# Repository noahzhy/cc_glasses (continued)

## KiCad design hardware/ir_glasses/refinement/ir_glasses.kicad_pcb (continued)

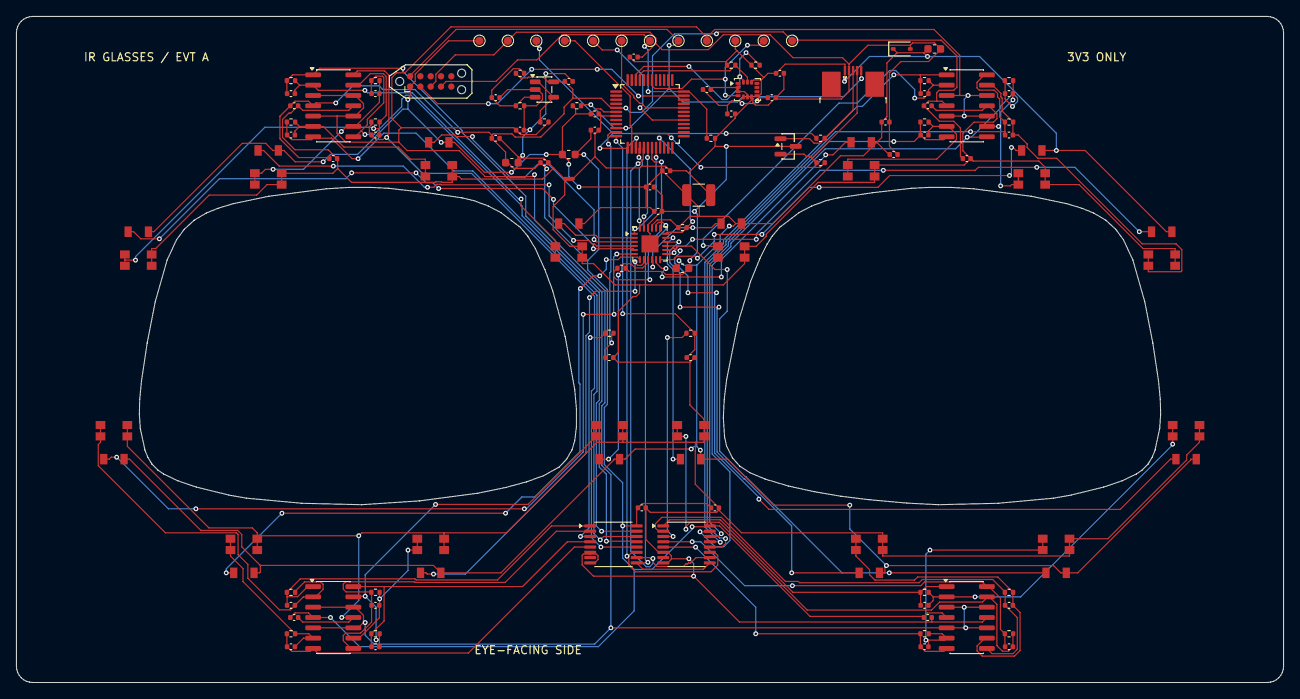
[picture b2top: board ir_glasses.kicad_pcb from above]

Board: 2 copper layers, 156.0 x 82.0 mm, 136 parts (0 on the bottom side), 79 nets.

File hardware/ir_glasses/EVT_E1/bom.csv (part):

Reference,Value,Footprint,Quantity,Populate,X_mm,Y_mm,Rotation_deg,Side,Manufacturer,MPN,LCSC
U9,STM32C031C6T6,IR_Glasses:LQFP-48_7x7mm_P0.5mm,1,Yes,110,63,0,front,STMicroelectronics,STM32C031C6T6,C5456218
U1,TLC59283RGER,IR_Glasses:Texas_RGE0024C_VQFN-24-1EP_4x4mm_P0.5mm_EP2.1x2.1mm,1,Yes,121,62,0,front,Texas Instruments,TLC59283RGER,C485815
U10,LSM6DS3TR-C,IR_Glasses:LGA-14_3x2.5mm_P0.5mm_LayoutBorder3x4y,1,Yes,110,71.3,0,front,STMicroelectronics,LSM6DS3TR-C,C967633
U6,TLV9061IDBVR,IR_Glasses:SOT-23-5,1,Yes,87,62,0,front,Texas Instruments,TLV9061IDBVR,C398358
J1,2492111-5,IR_Glasses:TE_2492111-5_1x05_P0.5mm_Horizontal,1,Yes,165,61.7,180,front,TE Connectivity,2492111-5,
J2,TC2050-IDC-NL / ARM2010,IR_Glasses:Tag-Connect_TC2050-IDC-NL_2x05_P1.27mm_Vertical,1,PCB pads only,55.5,61,0,front,,,
U11,"PESD3V3L2BT,215",IR_Glasses:SOT-23,1,Yes,167.5,67.0,0,front,Nexperia,"PESD3V3L2BT,215",C55440
D17,"PESD5V0S1BA,115",IR_Glasses:D_SOD-323,1,Yes,159.0,60.0,90,front,Nexperia,"PESD5V0S1BA,115",C19224
FB1,600R@100MHz 500mA,IR_Glasses:L_0603_1608Metric,1,Yes,89.0,67.0,0,front,Murata,BLM18AG601SN1D,C19330
NT1,AGND-GND star,IR_Glasses:NetTie-2_SMD_Pad0.5mm,1,PCB pads only,92.0,67.0,0,front,,,
R1,2.67k,IR_Glasses:R_0402_1005Metric,1,Yes,125.75,63.25,90,front,Viking,ARG02FTC2671,C284464
R2,10k,IR_Glasses:R_0402_1005Metric,1,Yes,85.0,59.5,0,front,UNI-ROYAL,0402WGF1002TCE,C25744
R3,10k,IR_Glasses:R_0402_1005Metric,1,Yes,86.0,64.5,0,front,UNI-ROYAL,0402WGF1002TCE,C25744
R4,10k,IR_Glasses:R_0402_1005Metric,1,Yes,103.5,61.0,0,front,UNI-ROYAL,0402WGF1002TCE,C25744
R5,100k,IR_Glasses:R_0402_1005Metric,1,Yes,115.8,61.0,90,front,UNI-ROYAL,0402WGF1003TCE,C25741
R6,4.7k,IR_Glasses:R_0402_1005Metric,1,Yes,113.0,70.0,0,front,UNI-ROYAL,0402WGF4701TCE,C25900
R7,4.7k,IR_Glasses:R_0402_1005Metric,1,Yes,113.5,72.0,90,front,UNI-ROYAL,0402WGF4701TCE,C25900
R8,22,IR_Glasses:R_0402_1005Metric,1,Yes,154.0,66.0,0,front,UNI-ROYAL,0402WGF220JTCE,C25092
R9,22,IR_Glasses:R_0402_1005Metric,1,Yes,170.0,69.5,0,front,UNI-ROYAL,0402WGF220JTCE,C25092
R10,10k,IR_Glasses:R_0402_1005Metric,1,Yes,125.75,60.0,90,front,UNI-ROYAL,0402WGF1002TCE,C25744
R11,100,IR_Glasses:R_0402_1005Metric,1,Yes,102.0,67.0,0,front,UNI-ROYAL,0402WGF1000TCE,C25076
R12,100,IR_Glasses:R_0402_1005Metric,1,Yes,116.0,67.0,90,front,UNI-ROYAL,0402WGF1000TCE,C25076
R13,47,IR_Glasses:R_0402_1005Metric,1,Yes,89.75,60.0,90,front,UNI-ROYAL,0402WGF470JTCE,C25118
U2,TLV9064IPWR,IR_Glasses:TSSOP-14_4.4x5mm_P0.65mm,1,Yes,77.5,60.5,0,front,Texas Instruments,TLV9064IPWR,C779410
U3,TLV9064IPWR,IR_Glasses:TSSOP-14_4.4x5mm_P0.65mm,1,Yes,67,61.4,0,front,Texas Instruments,TLV9064IPWR,C779410
PD1,PD15-22B/TR8,IR_Glasses:Everlight_PD15_22B,1,Yes,99.1474,94.9322,69.734,front,Everlight,PD15-22B/TR8,C161211
D1,IR11-21C/TR8,IR_Glasses:Everlight_IR11_21C,1,Yes,97.2266,99.389,61.38,front,Everlight,IR11-21C/TR8,C16745
RF1,100k,IR_Glasses:R_0402_1005Metric,1,Yes,72.888,58.875,90,front,UNI-ROYAL,0402WGF1003TCE,C25741
CF1,22p C0G,IR_Glasses:C_0402_1005Metric,1,Yes,72.888,60.875,90,front,FH,0402CG220J500NT,C1555
PD2,PD15-22B/TR8,IR_Glasses:Everlight_PD15_22B,1,Yes,86.2915,106.4166,9.481,front,Everlight,PD15-22B/TR8,C161211
D2,IR11-21C/TR8,IR_Glasses:Everlight_IR11_21C,1,Yes,81.3647,107.0997,6.53,front,Everlight,IR11-21C/TR8,C16745
RF2,100k,IR_Glasses:R_0402_1005Metric,1,Yes,74.638,63.875,0,front,UNI-ROYAL,0402WGF1003TCE,C25741
CF2,22p C0G,IR_Glasses:C_0402_1005Metric,1,Yes,72.888,62.875,90,front,FH,0402CG220J500NT,C1555
PD3,PD15-22B/TR8,IR_Glasses:Everlight_PD15_22B,1,Yes,65.5404,106.8475,-7.387,front,Everlight,PD15-22B/TR8,C161211
D3,IR11-21C/TR8,IR_Glasses:Everlight_IR11_21C,1,Yes,60.667,106.0473,-11.779,front,Everlight,IR11-21C/TR8,C16745
RF3,100k,IR_Glasses:R_0402_1005Metric,1,Yes,82.112,62.125,90,front,UNI-ROYAL,0402WGF1003TCE,C25741
CF3,22p C0G,IR_Glasses:C_0402_1005Metric,1,Yes,82.112,60.125,90,front,FH,0402CG220J500NT,C1555
PD4,PD15-22B/TR8,IR_Glasses:Everlight_PD15_22B,1,Yes,49.5328,98.7372,-65.946,front,Everlight,PD15-22B/TR8,C161211
D4,IR11-21C/TR8,IR_Glasses:Everlight_IR11_21C,1,Yes,48.0093,94.1124,-74.093,front,Everlight,IR11-21C/TR8,C16745
RF4,100k,IR_Glasses:R_0402_1005Metric,1,Yes,82.612,58.375,0,front,UNI-ROYAL,0402WGF1003TCE,C25741
CF4,22p C0G,IR_Glasses:C_0402_1005Metric,1,Yes,83.362,60.125,90,front,FH,0402CG220J500NT,C1555
PD5,PD15-22B/TR8,IR_Glasses:Everlight_PD15_22B,1,Yes,45.494200000000006,78.5897,-89.524,front,Everlight,PD15-22B/TR8,C161211
D5,IR11-21C/TR8,IR_Glasses:Everlight_IR11_21C,1,Yes,46.0878,73.8218,-105.15,front,Everlight,IR11-21C/TR8,C16745
RF5,100k,IR_Glasses:R_0402_1005Metric,1,Yes,62.388,59.775,90,front,UNI-ROYAL,0402WGF1003TCE,C25741
CF5,22p C0G,IR_Glasses:C_0402_1005Metric,1,Yes,64.138,58.025,0,front,FH,0402CG220J500NT,C1555
PD6,PD15-22B/TR8,IR_Glasses:Everlight_PD15_22B,1,Yes,57.9682,66.4324,-167.812,front,Everlight,PD15-22B/TR8,C161211
D6,IR11-21C/TR8,IR_Glasses:Everlight_IR11_21C,1,Yes,62.8597,65.8002,-174.743,front,Everlight,IR11-21C/TR8,C16745
RF6,100k,IR_Glasses:R_0402_1005Metric,1,Yes,62.388,63.025,90,front,UNI-ROYAL,0402WGF1003TCE,C25741
CF6,22p C0G,IR_Glasses:C_0402_1005Metric,1,Yes,65.888,64.775,0,front,FH,0402CG220J500NT,C1555
PD7,PD15-22B/TR8,IR_Glasses:Everlight_PD15_22B,1,Yes,80.0574,65.60249999999999,176.212,front,Everlight,PD15-22B/TR8,C161211
D7,IR11-21C/TR8,IR_Glasses:Everlight_IR11_21C,1,Yes,84.9772,66.1358,172.509,front,Everlight,IR11-21C/TR8,C16745
RF7,100k,IR_Glasses:R_0402_1005Metric,1,Yes,69.862,64.775,0,front,UNI-ROYAL,0402WGF1003TCE,C25741
CF7,22p C0G,IR_Glasses:C_0402_1005Metric,1,Yes,71.612,63.025,90,front,FH,0402CG220J500NT,C1555
PD8,PD15-22B/TR8,IR_Glasses:Everlight_PD15_22B,1,Yes,102.2158,73.9515,106.619,front,Everlight,PD15-22B/TR8,C161211
D8,IR11-21C/TR8,IR_Glasses:Everlight_IR11_21C,1,Yes,102.5903,78.7863,87.338,front,Everlight,IR11-21C/TR8,C16745
RF8,100k,IR_Glasses:R_0402_1005Metric,1,Yes,69.862,58.025,0,front,UNI-ROYAL,0402WGF1003TCE,C25741
CF8,22p C0G,IR_Glasses:C_0402_1005Metric,1,Yes,71.612,59.775,90,front,FH,0402CG220J500NT,C1555
U7,TMUX1308PWR,IR_Glasses:TSSOP-16_4.4x5mm_P0.65mm,1,Yes,95,62,0,front,Texas Instruments,TMUX1308PWR,C970231
U4,TLV9064IPWR,IR_Glasses:TSSOP-14_4.4x5mm_P0.65mm,1,Yes,142.5,60.5,0,front,Texas Instruments,TLV9064IPWR,C779410
U5,TLV9064IPWR,IR_Glasses:TSSOP-14_4.4x5mm_P0.65mm,1,Yes,153,61.4,0,front,Texas Instruments,TLV9064IPWR,C779410
PD9,PD15-22B/TR8,IR_Glasses:Everlight_PD15_22B,1,Yes,120.8321,94.9333,-70.297,front,Everlight,PD15-22B/TR8,C161211
D9,IR11-21C/TR8,IR_Glasses:Everlight_IR11_21C,1,Yes,122.806,99.4398,-61.268,front,Everlight,IR11-21C/TR8,C16745
RF9,100k,IR_Glasses:R_0402_1005Metric,1,Yes,137.888,58.875,90,front,UNI-ROYAL,0402WGF1003TCE,C25741
CF9,22p C0G,IR_Glasses:C_0402_1005Metric,1,Yes,137.888,60.875,90,front,FH,0402CG220J500NT,C1555
PD10,PD15-22B/TR8,IR_Glasses:Everlight_PD15_22B,1,Yes,133.70850000000002,106.4166,-9.481,front,Everlight,PD15-22B/TR8,C161211
D10,IR11-21C/TR8,IR_Glasses:Everlight_IR11_21C,1,Yes,138.6353,107.0997,-6.53,front,Everlight,IR11-21C/TR8,C16745
RF10,100k,IR_Glasses:R_0402_1005Metric,1,Yes,137.888,62.875,90,front,UNI-ROYAL,0402WGF1003TCE,C25741
CF10,22p C0G,IR_Glasses:C_0402_1005Metric,1,Yes,136.638,62.125,90,front,FH,0402CG220J500NT,C1555
PD11,PD15-22B/TR8,IR_Glasses:Everlight_PD15_22B,1,Yes,154.4596,106.8475,7.387,front,Everlight,PD15-22B/TR8,C161211
D11,IR11-21C/TR8,IR_Glasses:Everlight_IR11_21C,1,Yes,159.333,106.0473,11.779,front,Everlight,IR11-21C/TR8,C16745
RF11,100k,IR_Glasses:R_0402_1005Metric,1,Yes,145.362,63.875,0,front,UNI-ROYAL,0402WGF1003TCE,C25741
CF11,22p C0G,IR_Glasses:C_0402_1005Metric,1,Yes,147.112,62.125,90,front,FH,0402CG220J500NT,C1555
PD12,PD15-22B/TR8,IR_Glasses:Everlight_PD15_22B,1,Yes,170.4672,98.7372,65.946,front,Everlight,PD15-22B/TR8,C161211
D12,IR11-21C/TR8,IR_Glasses:Everlight_IR11_21C,1,Yes,171.9907,94.1124,74.093,front,Everlight,IR11-21C/TR8,C16745
RF12,100k,IR_Glasses:R_0402_1005Metric,1,Yes,147.112,58.875,90,front,UNI-ROYAL,0402WGF1003TCE,C25741
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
